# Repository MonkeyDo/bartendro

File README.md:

Original README (2010)
============

Programs for the various systems of the Bartendro drink dispensing robot.

Created by [Pierre Michael](https://github.com/pmich) and [Robert Kaye](https://github.com/mayhem) ~ Copyright (c) Party Robotics 2010-2013

All of the source code in this repository is licensed under the GNU Public License 2.0.
The hardware schematic and layouts are licensed using the Creative Commons 
Attribution-ShareAlike 3.0 Unported license.

The source tree is laid out as follows:
  * firmware - source code (C) for the dispenser and router boards
  * scripts  - scripts to make running the bartendro software easier
  * ui       - web interface for the bot, written in python.

New README (2026)
============

## Requirements
To build your own fully-functional Bartendro cocktail robot requires various components: a Raspberry Pi (3-B or 4), custom main router board created by Party Robotics, several peristaltic pump dispensers each with motor and mini-router boards, power supply, cabling, tubing and lots of liquids. The open hardware schematics for PCBs and other components these can be found in the [original repository in the /hardware folder.](https://github.com/partyrobotics/bartendro).

This project requires that you build your own Bartendro or procure one from a former Kickstarter backer. Without it the code in this repository will only work in `--software-only` mode if the physical elements are not all connected.

### Code has been tested as working on
* [x] Raspberry Pi Os (Legacy, 32-bit) / Buster-armhf-lite (June 2019) / Note: only by using SD card image produced in 2021, Buster no longer supported by Raspbian
* [x] Raspberry Pi OS (Legacy, 32-bit) / Bullseye-armhf-lite (Aug 2021)
* [ ] Raspberry Pi OS (Legacy, 32-bit) / Bookworm-armhf-lite (June 2023)
* [ ] Raspberry Pi OS (Legacy, 32-bit) / trixie-armhf-lite (Aug 2025)
* [ ] Any arm64-lite version of Raspberry Pi OS / `¯\_ (ツ)_/¯  will it run?`

Convenience link to the [official distro image archive for the 32-bit Raspiberry Pi OS](https://downloads.raspberrypi.com/raspios_lite_armhf/images/)

### Releases
- 2021: .img to be flashed onto an SD card (Working on RPI 3 and 4, based on RaspiOS Bullseye 32-bit): [v-2021-05-21](https://github.com/partyrobotics/bartendro/releases/tag/v-2021-05-21)
- 2026: A snapshot of Bartendro as it was running in 2021 with python 2, before we merge in some improvements that were added at a later date. Removes "turbo mode" and "sobriety check" features that we are not going to use: [2021-python2](https://github.com/MonkeyDo/bartendro/releases/tag/2021-python2) 
- 2026: Continued improvements and multiple cocktails were served whilst debugging the new code: [TBC - release is currently being mixed](https://www.youtube.com/watch?v=XfELJU1mRMg)

## Getting started

- Read the [history of Bartendro](https://github.com/MonkeyDo/bartendro/blob/master/docs/history.md)
- Read our [Start Here guide](https://github.com/MonkeyDo/bartendro/blob/master/docs/2026-start-here.md)
- Read the [Install Guide](https://github.com/MonkeyDo/bartendro/blob/master/docs/2026-install-guide.md)
- Read the [User Guide](https://github.com/MonkeyDo/bartendro/blob/master/docs/2026-user-guide.md)
- Get hold of or build your own Bartendro (see Requirements section above)
- Flash one of the Releases listed above onto a SD card with at least 4GB of memory and follow the [Install Guide](https://github.com/MonkeyDo/bartendro/blob/master/docs/2026-install-guide.md)
- Once you have the hardware setup and working follow the [User Guide](https://github.com/MonkeyDo/bartendro/blob/master/docs/2026-user-guide.md) to get your Bartendro calibrated and serving robo-cocktails!

Links to relevant code repositories
============

1. Archived bartendro code that can be found in [https://github.com/partyrobotics/bartendro](https://github.com/partyrobotics/bartendro) - we did not fork the `hardware` and `tsb` sections as these are the schematics for the PCB boards and legacy code the prototype Tequila Sunrise Bot.
2. An open sourced metal frame for holding 3 pumps and all the boards [made by Wyolum.](https://github.com/wyolum/bartendro_frame)
3. Rob's personal repos with additional configuration scripts (outdated): [mayhem/bartendro-config](https://github.com/mayhem/bartendro-config)
4. Rob's collection of BASH scripts to deploy bartendro: [mayhem/bartendro-deploy](https://github.com/mayhem/bartendro-deploy)
5. Ansible Cookbooks from 2013: [mayhem/bartendro-chef-cookbooks](https://github.com/mayhem/bartendro-chef-cookbooks)

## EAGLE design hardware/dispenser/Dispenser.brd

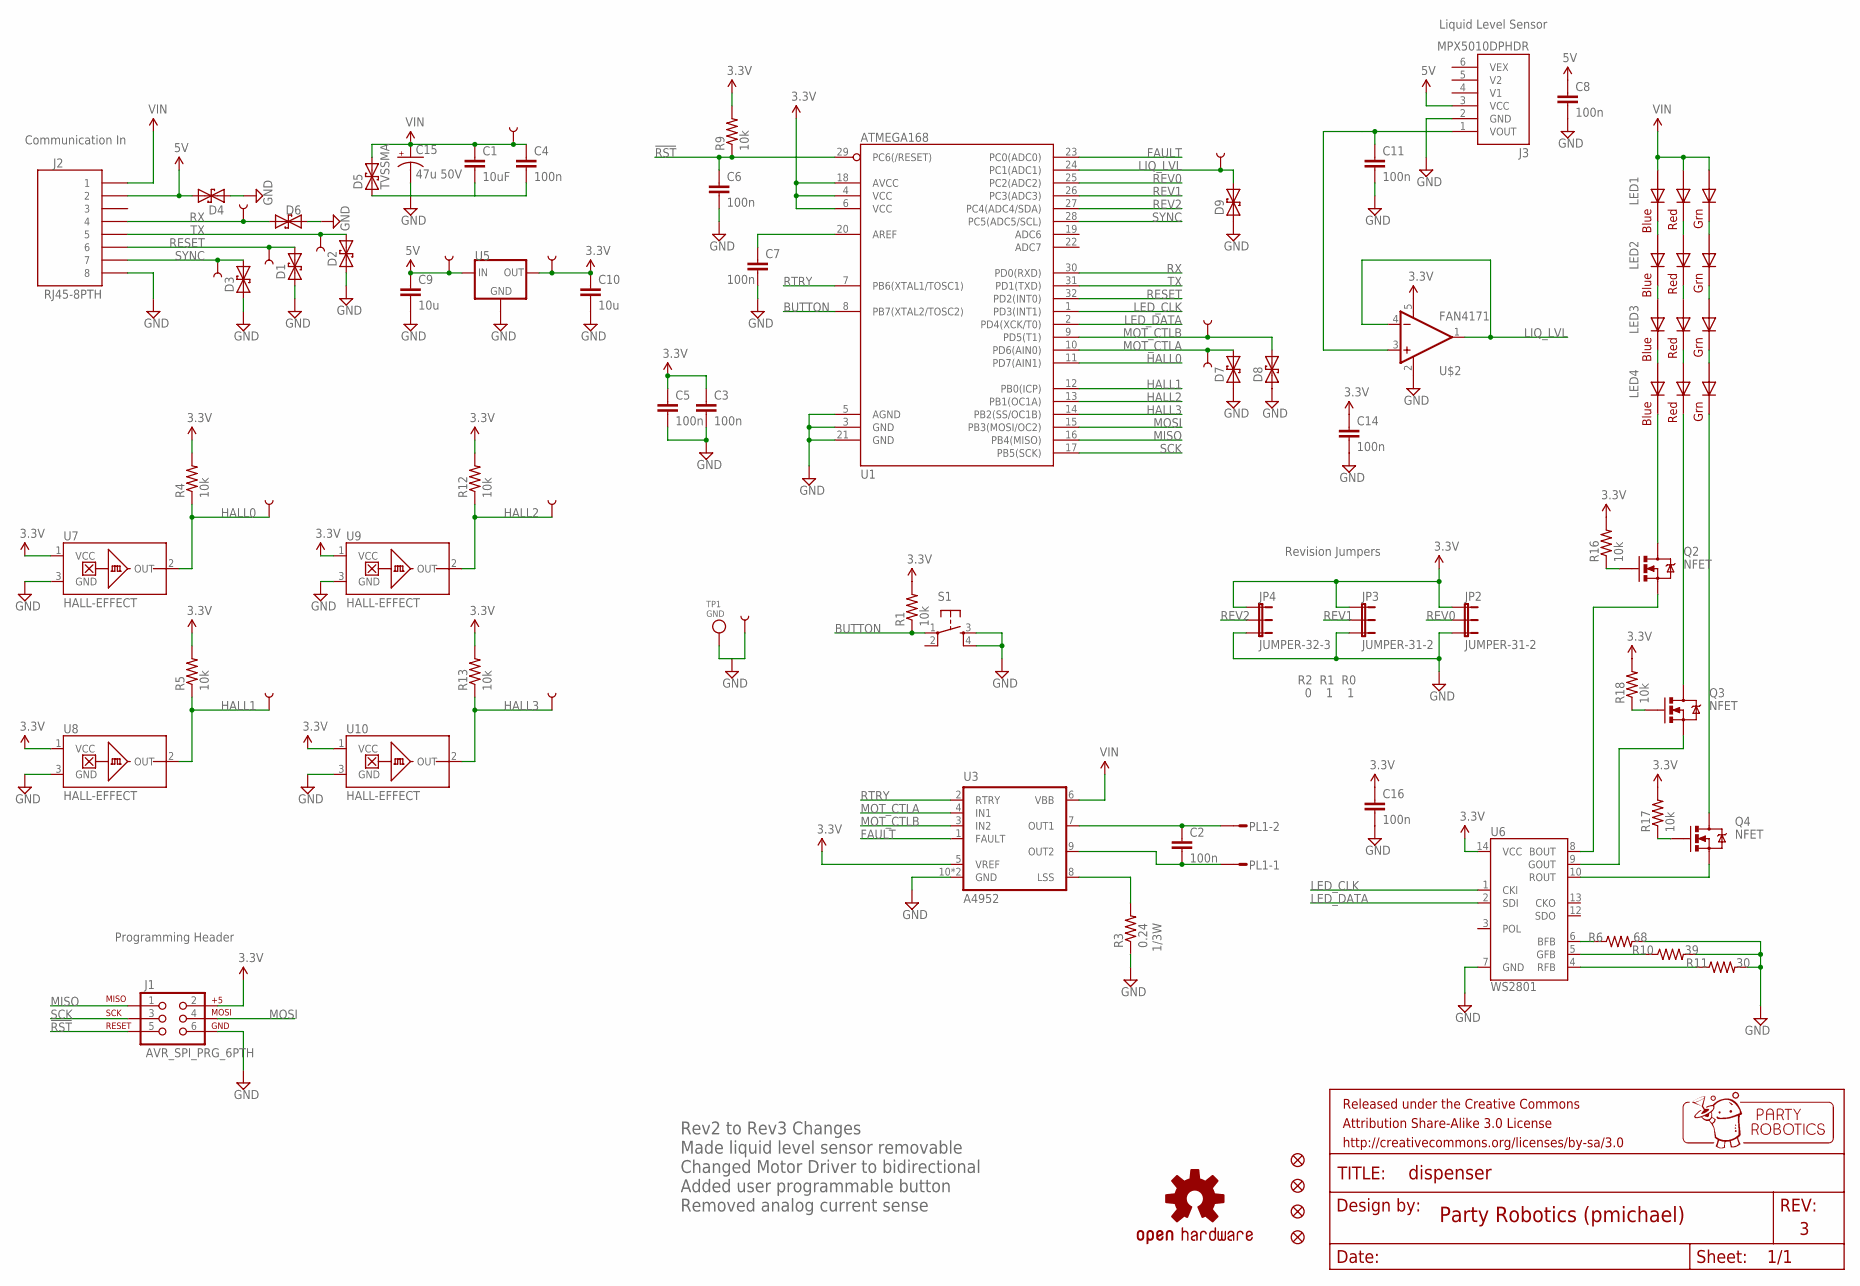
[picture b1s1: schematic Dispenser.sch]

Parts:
C1: 10uF; 1206
C2, C3, C4, C5, C6, C7, C8, C11, C14, C16: 100n; 0603-CAP
C9, C10: 10u; 0603-CAP
C15: 47u 50V; PANASONIC_D
D1, D2, D3, D4, D6, D7, D8, D9: TVSSOD-923; SOD-923
D5: TVSSMA; SMA-DIODE
FRAME3: FRAME-LETTER; CREATIVE_COMMONS
J1: AVR_SPI_PRG_6PTH; 2X3
J2: RJ45-8PTH; RJ45-8
J3: MPX5010DPHDR; MPX5010_HDR
JP2, JP3: JUMPER-31-2; SJ_3_PASTE1&2
JP4: JUMPER-32-3; SJ_3_PASTE2&3
JP5, JP6, JP7, JP8: FIDUCIAL1X2; FIDUCIAL-1X2
LED1, LED2, LED3, LED4: RGBLED5050
PL1: DF3-02P; DF3P-02
Q2, Q3, Q4: NFET; SOT23-3
R1, R4, R5, R9, R12, R13, R16, R17, R18: 10k; 0603-RES
R3: 0.24; 0805
R6: 68; 0603-RES
R10: 39; 0603-RES
R11: 30; 0603-RES
S1: TAC_SWITCHSMD; TACTILE_SWITCH_SMD
TP1: GND; TESTPOINT_SMT
TP2, TP3, TP4, TP5, TP6, TP13, TP14, TP15, TP16: TEST-POINT0.08; PAD_0.08
TP7, TP8, TP9, TP10, TP11, TP12: TEST-POINT3X5; PAD.03X.05
U1: ATMEGA168; TQFP32-08
U3: A4952; MSOP-10-GNDPAD
U5: VREG-5V-LDO-AP1117SOT89-3L; SOT89-3L
U6: WS2801; SOP-14
U7, U8, U9, U10: HALL-EFFECT; SOT23-3
U$1: OSHW-LOGOM; OSHW-LOGO-M
U$2: FAN4171; SOT23-5

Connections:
1/3W: R3.2, U3.8 (LSS)
3.3V: C3.1, C5.1, C10.1, C14.1, C16.1, J1.2, JP2.1, JP3.1, JP4.1, R1.2, R4.2, R5.2, R9.2, R12.2, R13.2, R16.2, R17.2, R18.2, TP16.P$1, U1.4 (VCC), U1.6 (VCC), U1.18 (AVCC), U3.5 (VREF), U5.2 (OUT), U5.2.1 (OUT), U6.14 (VCC), U7.1 (VCC), U8.1 (VCC), U9.1 (VCC), U10.1 (VCC), U$2.5 (V+)
5V: C8.1, C9.1, D4.C (2), J2.2, J3.3 (VCC), TP3.P$1, U5.3 (IN)
!RST: C6.1, J1.5, R9.1, U1.29 (PC6(/RESET))
BLUE: Q2.2 (S), U6.8 (BOUT)
BUTTON: R1.1, S1.1, U1.8 (PB7(XTAL2/TOSC2))
FAULT: U1.23 (PC0(ADC0)), U3.1 (FAULT)
GND: C1.2, C3.2, C4.2, C5.2, C6.2, C7.2, C8.2, C9.2, C10.2, C11.2, C14.2, C15.-, C16.2, D1.A (1), D2.A (1), D3.A (1), D4.A (1), D5.A (1), D6.A (1), D7.A (1), D8.A (1), D9.A (1), J1.6, J2.8, J3.2 (GND), JP2.3, JP3.3, JP4.3, R3.1, R6.2, R10.2, R11.2, S1.3, S1.4, TP1.P$1, TP2.P$1, U1.3 (GND), U1.5 (AGND), U1.21 (GND), U3.10 (GND), U3.GND, U5.1 (GND), U6.7 (GND), U7.3 (GND), U8.3 (GND), U9.3 (GND), U10.3 (GND), U$2.2 (V-)
GREEN: Q3.2 (S), U6.9 (GOUT)
HALL0: R4.1, TP10.P$1, U1.11 (PD7(AIN1)), U7.2 (OUT)
HALL1: R5.1, TP11.P$1, U1.12 (PB0(ICP)), U8.2 (OUT)
HALL2: R12.1, TP9.P$1, U1.13 (PB1(OC1A)), U9.2 (OUT)
HALL3: R13.1, TP12.P$1, U1.14 (PB2(SS/OC1B)), U10.2 (OUT)
LED_CLK: U1.1 (PD3(INT1)), U6.1 (CKI)
LED_DATA: U1.2 (PD4(XCK/T0)), U6.2 (SDI)
LIQ_LVL: D9.C (2), TP14.P$1, U1.24 (PC1(ADC1)), U$2.1 (OUT), U$2.4 (-IN)
MISO: J1.1, U1.16 (PB4(MISO))
MOSI: J1.4, U1.15 (PB3(MOSI/OC2))
MOT_CTLA: D7.C (2), TP8.P$1, U1.10 (PD6(AIN0)), U3.4 (IN1)
MOT_CTLB: D8.C (2), TP7.P$1, U1.9 (PD5(T1)), U3.3 (IN2)
unnamed: C7.1, U1.20 (AREF)
unnamed: Q3.1 (G), R18.1
unnamed: Q4.1 (G), R17.1
unnamed: Q2.1 (G), R16.1
unnamed: R6.1, U6.6 (BFB)
unnamed: R10.1, U6.5 (GFB)
unnamed: R11.1, U6.4 (RFB)
unnamed: C2.1, PL1.2, U3.7 (OUT1)
unnamed: C2.2, PL1.1, U3.9 (OUT2)
unnamed: LED4.6 (BLUE_C), Q2.3 (D)
unnamed: LED4.5 (RED_C), Q3.3 (D)
unnamed: LED4.4 (GREEN_C), Q4.3 (D)
unnamed: Q4.2 (S), U6.10 (ROUT)
unnamed: C11.1, J3.1 (VOUT), U$2.3 (+IN)
unnamed: LED3.6 (BLUE_C), LED4.1 (BLUE_A)
unnamed: LED3.5 (RED_C), LED4.2 (RED_A)
unnamed: LED3.4 (GREEN_C), LED4.3 (GREEN_A)
unnamed: LED2.4 (GREEN_C), LED3.3 (GREEN_A)
unnamed: LED2.5 (RED_C), LED3.2 (RED_A)
unnamed: LED2.6 (BLUE_C), LED3.1 (BLUE_A)
unnamed: LED1.4 (GREEN_C), LED2.3 (GREEN_A)
unnamed: LED1.5 (RED_C), LED2.2 (RED_A)
unnamed: LED1.6 (BLUE_C), LED2.1 (BLUE_A)
RESET: D1.C (2), J2.6, TP13.P$1, U1.32 (PD2(INT0))
REV0: JP2.2, U1.25 (PC2(ADC2))
REV1: JP3.2, U1.26 (PC3(ADC3))
REV2: JP4.2, U1.27 (PC4(ADC4/SDA))
RTRY: U1.7 (PB6(XTAL1/TOSC1)), U3.2 (RTRY)
RX: D6.C (2), J2.4, TP4.P$1, U1.30 (PD0(RXD))
SCK: J1.3, U1.17 (PB5(SCK))
SYNC: D3.C (2), J2.7, TP15.P$1, U1.28 (PC5(ADC5/SCL))
TX: D2.C (2), J2.5, TP5.P$1, U1.31 (PD1(TXD))
VIN: C1.1, C4.1, C15.+, D5.C (2), J2.1, LED1.1 (BLUE_A), LED1.2 (RED_A), LED1.3 (GREEN_A), TP6.P$1, U3.6 (VBB)

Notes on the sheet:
Programming Header
Liquid Level Sensor
Party Robotics (pmichael)
Communication In
Revision Jumpers
R2 R1 R0
0 1 1
Rev2 to Rev3 Changes Made liquid level sensor removable Changed Motor Driver to bidirectional Added user programmable button Removed analog current sense

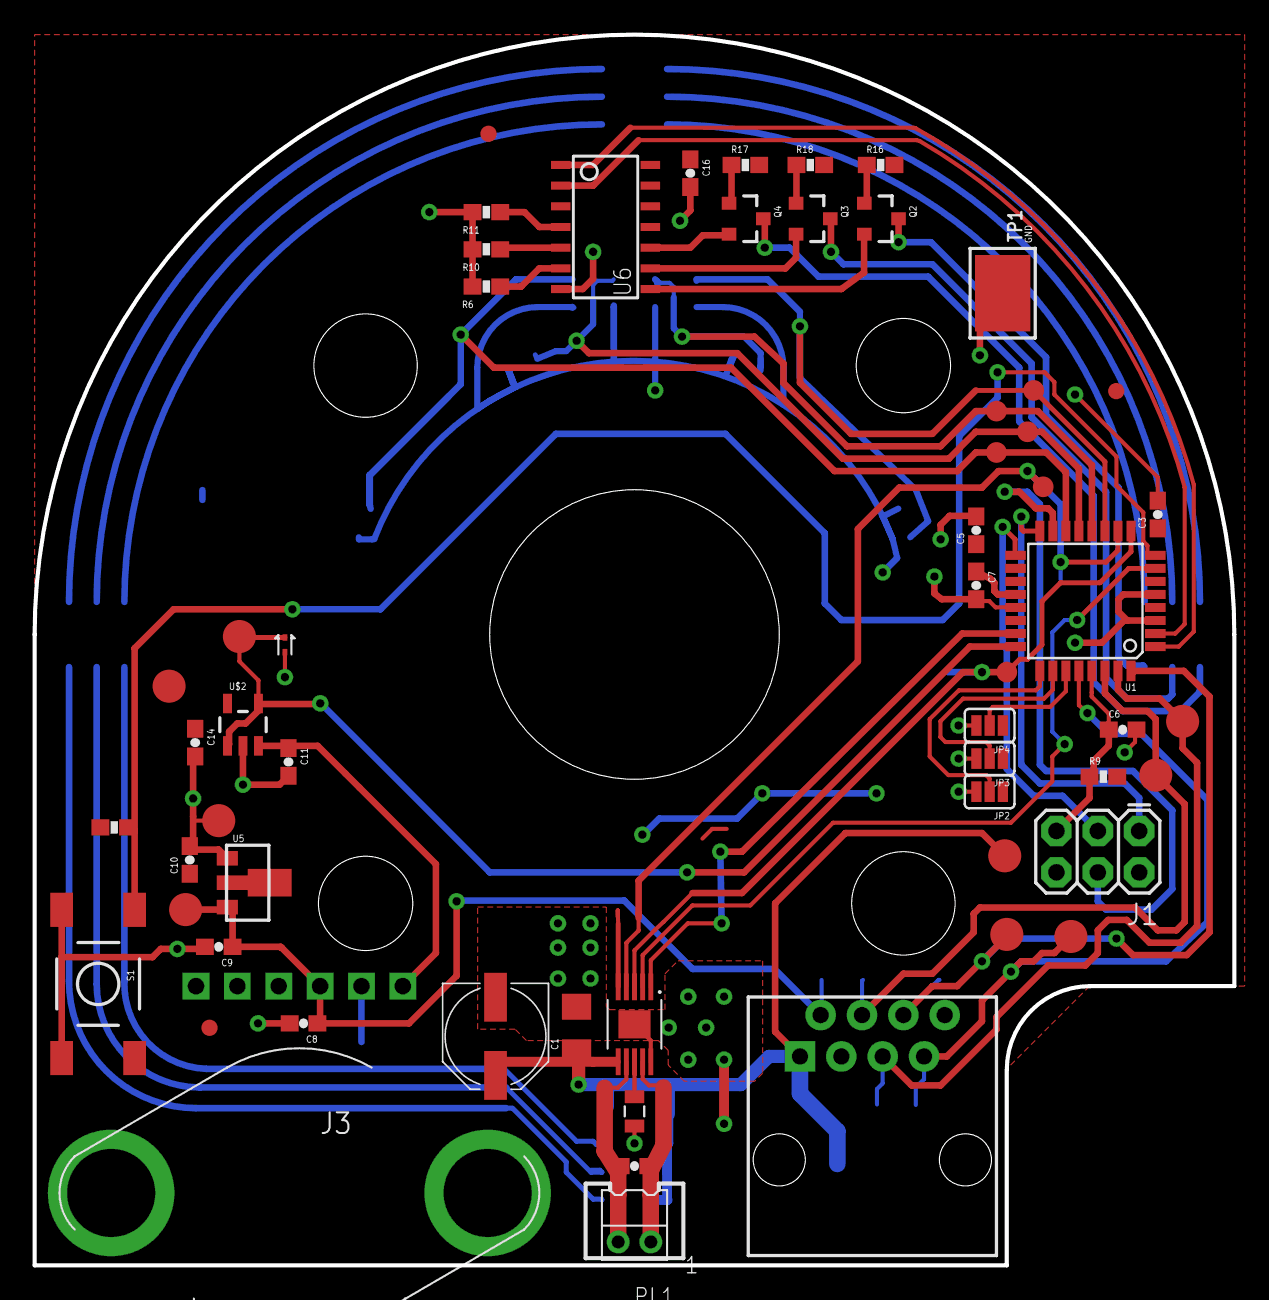
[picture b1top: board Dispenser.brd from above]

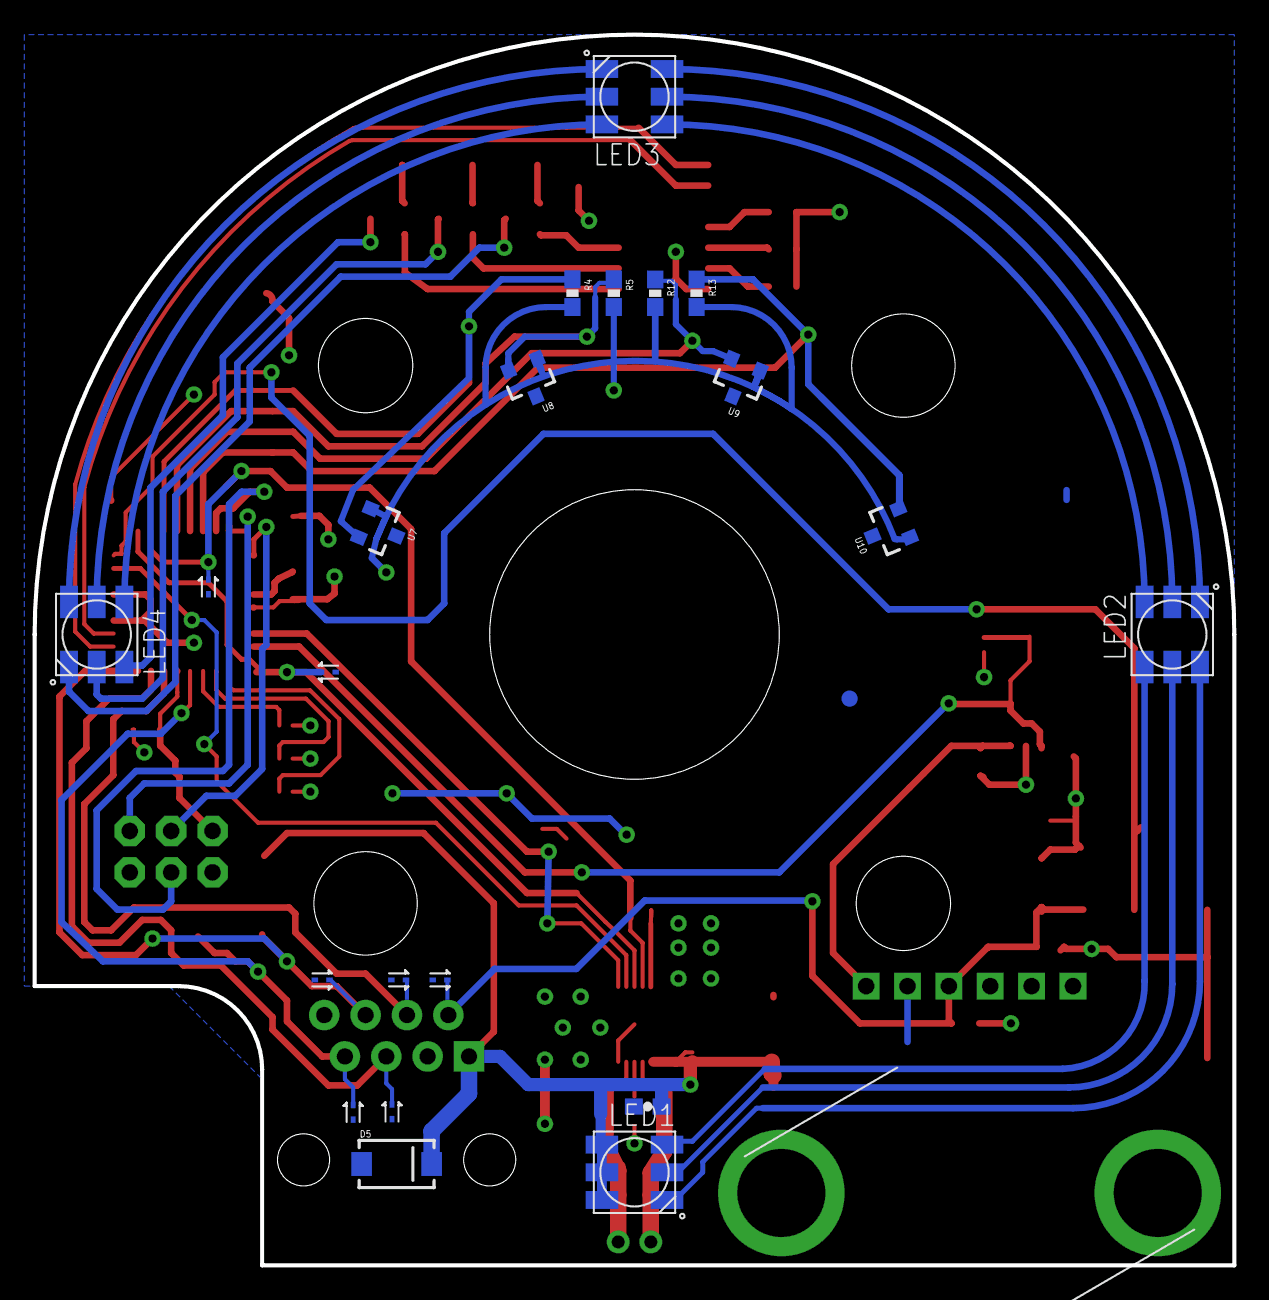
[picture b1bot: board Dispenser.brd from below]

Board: 2 copper layers, 73.7 x 75.6 mm, 82 parts (22 on the bottom side), 53 nets.

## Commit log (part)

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2025-11-28 Remove annoying bottle size drop downs and fix changing dispense button
2025-11-28 Show list of available drinks in dispenser menu
2025-11-28 Improve drinks view, add stats.
2025-11-28 Add a stats page to show how much boozing is going on
2025-11-28 Finish stats view
2025-11-28 Add a rough draft of the drinks planner
2025-11-28 Add support for deleting drinks.
2025-11-28 Making the planner work
2026-05-13 Archive dispenser factsheet
2026-05-13 moar things on roadmap
2026-05-13 Remove sobriety test
    This seems to have been hardoced disabled for over 10 years, and was only used for serving shots of top-shelf booze, whjich we are unlikely to here
2026-05-13 Renamed updated-sd-cards.txt to history.md
    Created a file to track the history of the projet and its various iterations
2026-05-13 Update history.md with video and press links
2026-05-13 Uploading Dispenser pin-out diagram
    extracted from archived version of partyrobotics.com
2026-05-13 renamed to dispenser-pinout-diagram.jpg for better sorting
2026-05-13 Uploading PDF guides for every bartendro machine and kit
    extracted from archived version of the partyrobotics website - thanks to the Internet Archive & Wayback Machine
2026-05-26 Formatting changes
    Auto-formatitng, updates for python3 imports and tools + a couple of small improvements that don't cahnge the functionality
2026-05-26 Manual liquid level setting
    This replaces the automatic liquid level sensing for a simpler solution of marking the current level avbailabel for each dispenser manually in the admin UI.
2026-05-26 Add spicy booze category and external ingredients
2026-05-26 Change status indicator LED
    Replaced with adafruit neopixel
2026-05-26 Pump adressing changes, replace usbtiny with avrispmkII
    No idea what this changes
2026-05-26 Update python packages
2026-05-26 Misc changes
2026-05-26 Replace home folder from robert to bartendro
    In scripts and daemon config
2026-05-26 updated install guide to better explain the Nerd Way method and link to the repository with the code
2026-05-26 Update ROADMAP.md > added other 32 bit versions of RaspiOS to test
2026-05-26 Added Before you Begin section to Install Guide
2026-05-26 fixing markdown
2026-05-26 removed extra .
2026-05-26 Updated docs roadmap
2026-05-26 formatting headers of history.md
2026-05-27 ROADMAP update
    Items were moved to strech goals, ticked some checkboxes for things we completed, and reordered things according to current prorities in the project
2026-05-27 more tweaks to ROADMAP
2026-05-27 New README.md
    includes old REAMDE and lots of links
2026-06-12 Update README.md
    added link to Raspiberry Pi OS archive
2026-06-12 Create 2026-install.sh
    Imported install.sh from /bartendro-config
    added comments to top about rework plan
2026-06-12 moved bash scripts to 2026-prepare.sh + commented it out here
2026-06-12 Create 2026-prepare.sh
    Importing content from 2026-install.sh
2026-06-12 Adding proposal comments in code for Monkey
    PROPOSAL: removing all make a user called bartendro part of the proces.... have everything point to /home/pi which is the default RPI OS user
2026-06-12 Added script - automated file backup flight-check
    # NEW: automated backups of the files we modify in this and install.sh
2026-06-12 mod: sudoers file
    Edited the line of script calling:
    `install -m 440 files/sudoers /etc/sudoers.d/90-bartendro`
    to:
    `echo "%sudo ALL=(ALL:ALL) NOPASSWD:ALL" | sudo install -m 440 /dev/stdin /etc/sudoers.d/90-bartendro`
    Removing the need for /files/sudoers to be included
2026-06-12 sub-group comments for each line + dhcpd.conf code
    replaced the cp of /files/dhcpd.conf to this:
    sudo install -m 0440 /dev/stdin /etc/dhcp/dhcpd.conf <<'EOF'
    ...
2026-06-12 Updated 'raspi-config' steps with details (OS: Buster)
2026-06-12 adding && apt-get upgrade to prepare.sh
2026-06-12 Adding disclaimer to Buster OS no longer being supported
2026-06-12 Fixed typo
2026-06-12 moved apt-get upgrade to post-dependency installation
2026-06-12 listed broken Python2 packages + changed git-core to git
2026-06-12 Update python dependencies
2026-06-12 Add installation and setup scripts
    Installs all the dependencies and git repo while internet is available, then the second script sets up the wifi access point and application, and the third script checks the status of the various cha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
2026-06-12 Install script: use the app setup scripts from git repo
2026-06-12 Try to fix permission issues
2026-06-12 Allow running as curl piped to bash
    Easy install script line `curl -fsSL https://raw.githubusercontent.com/MonkeyDo/bartendro/main/scripts/installation/setup_raspbian_image.sh | sudo bash`
2026-06-12 Protect agaisnt running on non-raspbian system
    additional protection to avoid someone fucking their computer configuration by mindlessly piping to sudo on the wrong machine.
2026-06-12 Update install instructions
2026-06-13 Fix SQLAlchemy statements
2026-06-15 Ignore .venv and logs folder
2026-06-15 Find database file if starting in another folder
2026-06-15 Update default DB file for deleted drink
    Commit 21e560132cb6292cc90988f23d5bf6d29e17b699 add the abvility to delete a drink, but also checks for a placeholder "deleted drink" and throws an erro otherwise.
    This updated default DB adds the required modification (moved the drink id=1 to a new ID and replaces ID 1 with the expected "Deleted Drink").
    Also contains new recipes and logs, but that's what it's gonna be.
2026-06-15 Add search functionality in drinks page
2026-06-15 Update DB upload/download for flask-sqlalchemy v3
    Flask-SQLAlchemy 3 does not expose a bound engine through db.session.bind so the closing-connection call needs to be updated.
    Also updates path to DB file like in commit 1b21998
2026-06-15 Add a restart scripts for convenience
2026-06-15 Call restart scripts from application when reboot required
2026-06-15 Fix serial port activation
    "do_serial 2" disables the login shell on serial and enables the serial hardware. This is available on older Raspberry Pi OS releases while do_serial_hw/do_serial_cons are not consistently available.
2026-06-15 Raspberry hardware setup: prefer non-interactive mode
    Fallback to interactive mode
2026-06-15 Restartscript: Accept arguments to pass to application
    for easy restart in debug mode or software-only mode
2026-06-15 Don't duplicate bartendro logs in journalctl
2026-06-15 Improve dispenser discovery routine
    Larger timeout, and retries, trying to solve dispensers communication issues
2026-06-15 Return an error when no liquid is dispensed for 5 seconds
    and show a useful message that the pumps might be badly installed
2026-06-16 Allow pouring drinks if boozes available
    Fix the state machine so that running out of one booze does not prevent dispensing cocktails that don't use that ingredient.
    Thepre-pour state was returning the wrong event code and putting the FSM into a broken state

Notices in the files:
hardware/dispenser/Dispenser.brd:
Released under the Creative Commons Attribution Share-Alike 3.0 License
http://creativecommons.org/licenses/by-sa/3.0
parts and their libraries:
SparkFun-Resistors: Licensing: CC v3.0 Share-Alike You are welcome to use this library for commercial purposes.
microbuilder: This work is placed in the public domain, and may be freely used for commercial and non-commercial work with the following conditions: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
